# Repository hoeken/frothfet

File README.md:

This is the hardware design repository for FrothFET.

For detailed documentation, please visit the [FrothFET documentation](https://frothfet.com).

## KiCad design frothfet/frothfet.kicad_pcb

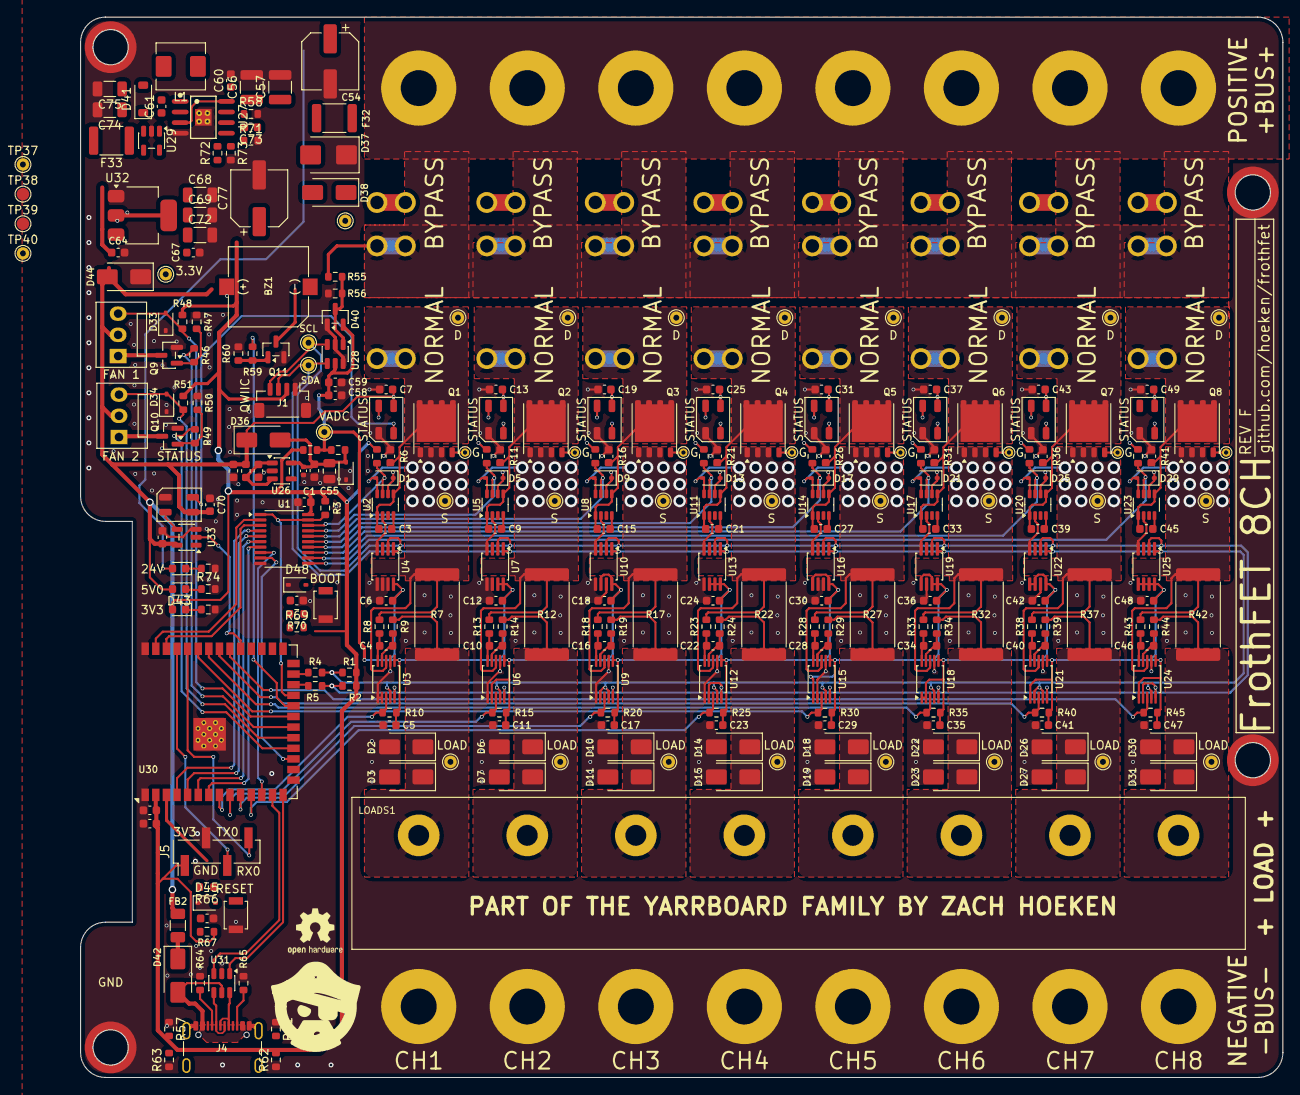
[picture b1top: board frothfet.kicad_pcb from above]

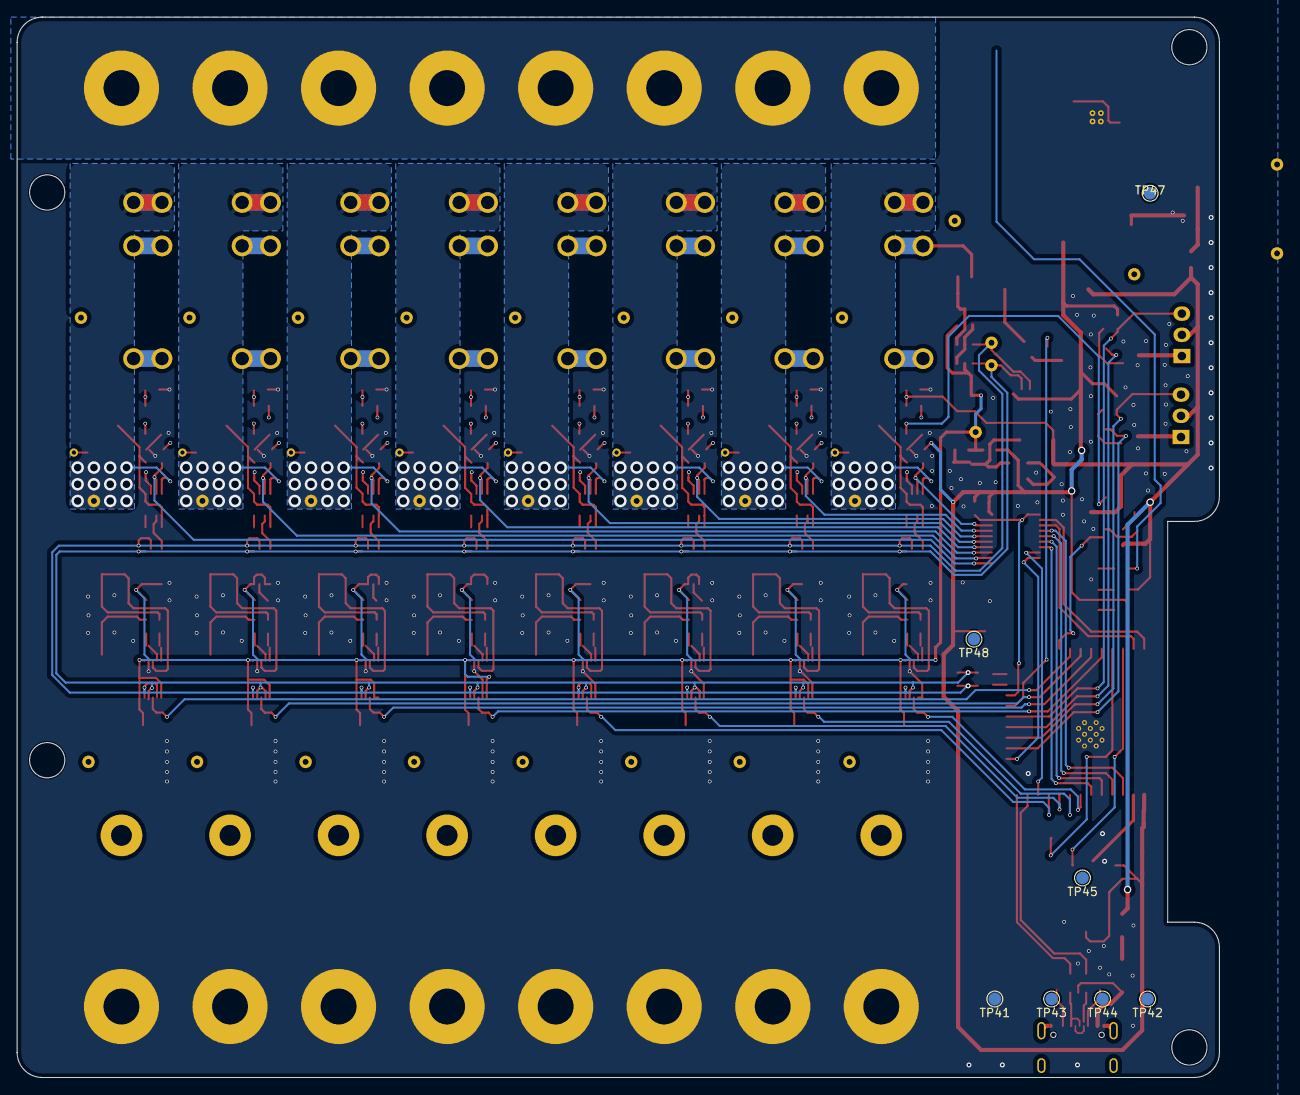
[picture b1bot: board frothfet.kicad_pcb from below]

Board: 4 copper layers, 144.0 x 127.0 mm, 344 parts (9 on the bottom side), 142 nets.

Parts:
ATC1: 20A; ATC Fuse
BZ1: Buzzer; Buzzer_FUET_9.6x9.6
C1, C2, C4, C5, C6, C7, C8, C10, C11, C12, C13, C14, C16, C17, C18, C19, C20, C22, C23, C24, C25, C26, C28, C29, C30, C31, C32, C34, C35, C36, C37, C38, C40, C41, C42, C43, C44, C46, C47, C48, C49, C51, C53, C59, C60, C61, C63, C65, C70: 100nF; C_0603_1608Metric
C3, C9, C15, C21, C27, C33, C39, C45: 220nF; C_0603_1608Metric
C50, C64, C66, C71: 1uF; C_0603_1608Metric
C52: 1nF; C_0402_1005Metric
C54: 100uF/50v; CP_Elec_6.3x7.7
C55: 10uF; C_0805_2012Metric
C56, C57: 10uF; C_1210_3225Metric
C58: 10uF; C_0603_1608Metric
C62: 22uF; C_0603_1608Metric
C67: 4.7uF; C_0603_1608Metric
C68, C69, C72: 100uF / 6.3v; C_1206_3216Metric
C73: 2.7nF; C_0603_1608Metric
C74, C75: 22uF; C_1206_3216Metric
C77: 220uF / 16v; CP_Elec_6.3x5.4
D1, D5, D9, D13, D17, D21, D25, D29: BZT52C20S; D_SOD-323
D2, D6, D10, D14, D18, D22, D26, D30, D36, D38: SS54; D_SMA
D3, D7, D11, D15, D19, D23, D27, D31: SMAJ30CA; D_SMA
D4, D8, D12, D16, D20, D24, D28, D32, D47: WS2812B-Mini; LED_WS2812B-Mini_PLCC4_3.5x3.5mm
D33, D34, D39, D45, D48: PESD3V3L1BA; D_SOD-323
D35, D43, D46: GREEN; LED_0603_1608Metric
D37: SMBJ30CA; D_SMB
D40: BAV199; SOT-23
D41: 1N4148W; D_SOD-123
D42: SS34; D_SMA
D44: SMAJ5.0A; D_SMA
F1, F2, F3, F5, F6, F7, F9, F10, F11, F13, F14, F15, F17, F18, F19, F21, F22, F23, F25, F26, F27, F29, F30, F31: T508; XFCN T508
F4, F8, F12, F16, F20, F24, F28: 20A; ATC Fuse
F32: 500mA; Fuse_1812_4532Metric
F33: mSMD200; Fuse_1812_4532Metric
FB1: BLM18AG121SN1D; L_0603_1608Metric
FB2: 1.5A; Fuse_1206_3216Metric
H1, H2, H3, H4: SMTSO30XXX
J1: Conn_01x04_MountingPin; JST_SH_BM04B-SRSS-TB_1x04-1MP_P1.00mm_Vertical
J2: Screw_Terminal_01x08; Frothfet Busbar Positive Rev E
J3: Screw_Terminal_01x08; Frothfet Busbar Negative Rev E
J4: USB_TYPE_C_16PIN; USB_C_Receptacle_GCT_USB4105-xx-A_16P_TopMnt_Horizontal
J5: Conn_01x04; PinHeader_1x04_P2.54mm_Vertical_SMD_Pin1Left
L1: 6.8uH; L_Chilisin_BMRA00050530
LOADS1: Screw_Terminal_01x08; KF78S-13.0-8P
LOGO1: Logo_Open_Hardware_Small; Logo Small
LOGO2: Logo_Open_Hardware_Small; OSHW-Logo2_7.3x6mm_SilkScreen
M1, M2: Fan_Tacho; FanPinHeader_1x03_P2.54mm_Vertical
Q1, Q2, Q3, Q4, Q5, Q6, Q7, Q8: BSC010N04LS; Infineon_PG-TDSON-8_6.15x5.15mm
Q9, Q10, Q11: AO3400A; SOT-23
R1, R2: 2.2k; R_0603_1608Metric
R3, R6, R10, R11, R15, R16, R20, R21, R25, R26, R30, R31, R35, R36, R40, R41, R45, R48, R51, R67, R70, R74: 10k; R_0603_1608Metric
R4, R5, R53, R54, R57, R61, R62, R63: 0R; R_0603_1608Metric
R7, R12, R17, R22, R27, R32, R37, R42: 2 mOhm; R_4020_10251Metric
R8, R9, R13, R14, R18, R19, R23, R24, R28, R29, R33, R34, R38, R39, R43, R44: 4.7R 1%; R_0603_1608Metric
R46, R49, R59, R66, R69: 100R; R_0603_1608Metric
R47, R50, R52, R60: 100k; R_0603_1608Metric
R55: 300K 0.1%; R_0603_1608Metric
R56: 22K 0.1%; R_0603_1608Metric
R58: 82k 1%; R_0603_1608Metric
R64, R65, R68: 5.1k; R_0603_1608Metric
R71: 24k; R_0603_1608Metric
R72: 62k 1%; R_0603_1608Metric
R73: 11.8k 1%; R_0603_1608Metric
SW1, SW2: SW_SPST_B3U-1000P
TP1, TP2, TP4, TP5, TP6, TP8, TP9, TP10, TP12, TP13, TP14, TP16, TP17, TP18, TP20, TP21, TP22, TP24, TP25, TP26, TP28, TP29, TP30, TP32, TP33, TP34, TP35, TP36, TP37, TP40, TP46: TestPoint_THTPad_D1.5mm_Drill0.7mm
TP3, TP7, TP11, TP15, TP19, TP23, TP27, TP31: TestPoint_THTPad_D1.0mm_Drill0.5mm
TP38, TP39, TP41, TP42, TP43, TP44, TP45, TP47, TP48: TestPoint; TestPoint_Pad_D1.5mm
U1: 74LVC541A; TSSOP-20_4.4x6.5mm_P0.65mm
U2, U5, U8, U11, U14, U17, U20, U23: LM74502H; SOT-23-8
U3, U6, U9, U12, U15, U18, U21, U24: INA226; VSSOP-10_3x3mm_P0.5mm
U4, U7, U10, U13, U16, U19, U22, U25: LM75BD; MSOP-8_3x3mm_P0.65mm
U26: TPS7A2033PDBVR; SOT-23-5
U27: RT7272BGSP; SOIC-8_L5.0-W4.0-P1.27-LS6.0-BL-EP2.0
U28: MCP3425A0T-ECH; SOT-23-6
U29: MAX40200AUK; SOT-23-5
U30: ESP32-S3-WROOM-1-N16R8; ESP32-S3-WROOM-1
U31: USBLC6-2SC6; SOT-23-6
U32: LDL1117S33R; SOT-223-3_TabPin2
U33: SN74LV1T34DBV; SOT-23-5

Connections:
+3.3V: C1.1, C62.1, C63.1, C67.1, C68.1, C69.1, C72.1, D46.2 (A), J1.2, J5.1, R1.2, R2.2, R3.1, R6.2, R11.2, R16.2, R21.2, R26.2, R31.2, R36.2, R41.2, R48.2, R51.2, R54.2, R67.1, R70.2, TP46.1, TP47.1, U1.20 (VCC), U30.2 (3V3), U32.2 (VO)
+3.3VADC: C5.1, C6.1, C11.1, C12.1, C17.1, C18.1, C23.1, C24.1, C29.1, C30.1, C35.1, C36.1, C41.1, C42.1, C47.1, C48.1, C58.1, C59.1, D40.2 (K), R10.2, R15.2, R20.2, R25.2, R30.2, R35.2, R40.2, R45.2, R53.2, R54.1, TP36.1, U3.6 (VS), U4.8 (+Vs), U6.2 (A0), U6.6 (VS), U7.7 (A0), U7.8 (+Vs), U9.6 (VS), U10.6 (A1), U10.8 (+Vs), U12.6 (VS), U13.6 (A1), U13.7 (A0), U13.8 (+Vs), U15.1 (A1), U15.6 (VS), U16.5 (A2), U16.8 (+Vs), U18.1 (A1), U18.2 (A0), U18.6 (VS), U19.5 (A2), U19.7 (A0), U19.8 (+Vs), U21.1 (A1), U21.6 (VS), U22.5 (A2), U22.6 (A1), U22.8 (+Vs), U24.1 (A1), U24.6 (VS), U25.5 (A2), U25.6 (A1), U25.7 (A0), U25.8 (+Vs), U28.5 (Vdd)
+5V: BZ1.1 (+), C7.2, C13.2, C19.2, C25.2, C31.2, C37.2, C43.2, C49.2, C50.1, C64.1, C65.1, C70.1, C77.1, D4.1 (VDD), D8.1 (VDD), D12.1 (VDD), D16.1 (VDD), D20.1 (VDD), D24.1 (VDD), D28.1 (VDD), D32.1 (VDD), D36.1 (K), D43.2 (A), D44.2 (A2), D47.1 (VDD), FB1.1, FB2.2, M1.2 (+), M2.2 (+), TP39.1, TP40.1, U29.5 (OUT), U32.3 (VI), U33.5 (VCC)
+24V: C54.1, F2.1, F6.1, F10.1, F14.1, F18.1, F22.1, F26.1, F30.1, F32.2, J2.1, J2.2, J2.3, J2.4, J2.5, J2.6, J2.7, J2.8, R55.2
/CHANNEL 1/LED_DOUT: D4.2 (DOUT), D8.4 (DIN)
/CHANNEL 1/LOAD_SWITCHED: D1.2 (A), F3.1, Q1.3 (S), R7.1, R8.2, TP5.1, U2.8 (SRC), U3.8 (Vbus)
/CHANNEL 1/LOAD_VSS: C2.1, C3.1, F1.1, Q1.1 (D), TP4.1, U2.1 (EN/UVLO), U2.5 (VS)
/CHANNEL 2/LED_DOUT: D8.2 (DOUT), D12.4 (DIN)
/CHANNEL 2/LOAD_SWITCHED: D5.2 (A), F7.1, Q2.3 (S), R12.1, R13.2, TP9.1, U5.8 (SRC), U6.8 (Vbus)
/CHANNEL 2/LOAD_VSS: C8.1, C9.1, F5.1, Q2.1 (D), TP8.1, U5.1 (EN/UVLO), U5.5 (VS)
/CHANNEL 3/LED_DOUT: D12.2 (DOUT), D16.4 (DIN)
/CHANNEL 3/LOAD_SWITCHED: D9.2 (A), F11.1, Q3.3 (S), R17.1, R18.2, TP13.1, U8.8 (SRC), U9.8 (Vbus)
/CHANNEL 3/LOAD_VSS: C14.1, C15.1, F9.1, Q3.1 (D), TP12.1, U8.1 (EN/UVLO), U8.5 (VS)
/CHANNEL 4/LED_DOUT: D16.2 (DOUT), D20.4 (DIN)
/CHANNEL 4/LOAD_SWITCHED: D13.2 (A), F15.1, Q4.3 (S), R22.1, R23.2, TP17.1, U11.8 (SRC), U12.8 (Vbus)
/CHANNEL 4/LOAD_VSS: C20.1, C21.1, F13.1, Q4.1 (D), TP16.1, U11.1 (EN/UVLO), U11.5 (VS)
/CHANNEL 5/LED_DOUT: D20.2 (DOUT), D24.4 (DIN)
/CHANNEL 5/LOAD_SWITCHED: D17.2 (A), F19.1, Q5.3 (S), R27.1, R28.2, TP21.1, U14.8 (SRC), U15.8 (Vbus)
/CHANNEL 5/LOAD_VSS: C26.1, C27.1, F17.1, Q5.1 (D), TP20.1, U14.1 (EN/UVLO), U14.5 (VS)
/CHANNEL 6/LED_DOUT: D24.2 (DOUT), D28.4 (DIN)
/CHANNEL 6/LOAD_SWITCHED: D21.2 (A), F23.1, Q6.3 (S), R32.1, R33.2, TP25.1, U17.8 (SRC), U18.8 (Vbus)
/CHANNEL 6/LOAD_VSS: C32.1, C33.1, F21.1, Q6.1 (D), TP24.1, U17.1 (EN/UVLO), U17.5 (VS)
/CHANNEL 7/LED_DOUT: D28.2 (DOUT), D32.4 (DIN)
/CHANNEL 7/LOAD_SWITCHED: D25.2 (A), F27.1, Q7.3 (S), R37.1, R38.2, TP29.1, U20.8 (SRC), U21.8 (Vbus)
/CHANNEL 7/LOAD_VSS: C38.1, C39.1, F25.1, Q7.1 (D), TP28.1, U20.1 (EN/UVLO), U20.5 (VS)
/CHANNEL 8/LOAD_SWITCHED: D29.2 (A), F31.1, Q8.3 (S), R42.1, R43.2, TP33.1, U23.8 (SRC), U24.8 (Vbus)
/CHANNEL 8/LOAD_VSS: C44.1, C45.1, F29.1, Q8.1 (D), TP32.1, U23.1 (EN/UVLO), U23.5 (VS)
/ESP32-S3/CC1_1: J4.A5 (CC1), R64.1
/ESP32-S3/CC2_1: J4.B5 (CC2), R65.1
/ESP32-S3/EN: R66.2, TP45.1, U30.3 (EN)
/ESP32-S3/ESP_RXD0: J5.4, U30.36 (RXD0)
/ESP32-S3/ESP_TXD0: J5.3, U30.37 (TXD0)
/ESP32-S3/ESP_USB+: U30.14 (USB_D+), U31.1 (I/O1)
/ESP32-S3/ESP_USB-: U30.13 (USB_D-), U31.3 (I/O2)
/ESP32-S3/GPIO0_BOOT: R69.2, TP48.1, U30.27 (IO0)
/ESP32-S3/GPIO1: U1.2 (A0), U30.39 (IO1)
/ESP32-S3/GPIO2: U1.3 (A1), U30.38 (IO2)
/ESP32-S3/GPIO4: U1.4 (A2), U30.4 (IO4)
/ESP32-S3/GPIO5: U1.5 (A3), U30.5 (IO5)
/ESP32-S3/GPIO6: U1.6 (A4), U30.6 (IO6)
/ESP32-S3/GPIO7: U1.7 (A5), U30.7 (IO7)
/ESP32-S3/GPIO8: U1.8 (A6), U30.12 (IO8)
/ESP32-S3/GPIO9: U1.9 (A7), U30.17 (IO9)
/ESP32-S3/GPIO21: R3.2, U1.1 (G1), U1.19 (G2), U30.23 (IO21)
/ESP32-S3/GPIO38: U30.31 (IO38), U33.2 (A)
/ESP32-S3/GPIO47: R4.1, U30.24 (IO47)
/ESP32-S3/GPIO48: R5.2, U30.25 (IO48)
/ESP32-S3/USB_D+: J4.A6 (D+), J4.B6 (D+), TP43.1, U31.6 (I/O1)
/ESP32-S3/USB_D-: J4.A7 (D-), J4.B7 (D-), TP44.1, U31.4 (I/O2)
/ESP32-S3/VBUS: D42.2 (A), J4.A4 (VBUS), J4.A9 (VBUS), J4.B4 (VBUS), J4.B9 (VBUS), TP42.1, U31.5 (VBUS)
/Power Supply/SW: C61.2, L1.1, U27.1 (SW)
ALERT1: R10.1, U3.3 (~Alert), U30.8 (IO15)
ALERT2: R15.1, U6.3 (~Alert), U30.9 (IO16)
ALERT3: R20.1, U9.3 (~Alert), U30.10 (IO17)
ALERT4: R25.1, U12.3 (~Alert), U30.11 (IO18)
ALERT5: R30.1, U15.3 (~Alert), U30.35 (IO42)
ALERT6: R35.1, U18.3 (~Alert), U30.34 (IO41)
ALERT7: R40.1, U21.3 (~Alert), U30.33 (IO40)
ALERT8: R45.1, U24.3 (~Alert), U30.32 (IO39)
CHANNEL_LEDS: D4.4 (DIN), D47.2 (DOUT)
FAN_MOSFET1: R46.2, U30.20 (IO12)
FAN_MOSFET2: R49.2, U30.18 (IO10)
FAN_TACH1: D33.2 (A2), M1.3 (Tacho), R48.1, U30.21 (IO13)
FAN_TACH2: D34.2 (A2), M2.3 (Tacho), R51.1, U30.19 (IO11)
GND: C1.2, C2.2, C5.2, C6.2, C7.1, C8.2, C11.2, C12.2, C13.1, C14.2, C17.2, C18.2, C19.1, C20.2, C23.2, C24.2, C25.1, C26.2, C29.2, C30.2, C31.1, C32.2, C35.2, C36.2, C37.1, C38.2, C41.2, C42.2, C43.1, C44.2, C47.2, C48.2, C49.1, C50.2, C51.2, C52.2, C53.2, C54.2, C55.2, C56.2, C57.2, C58.2, C59.2, C60.2, C62.2, C63.2, C64.2, C65.2, C66.2, C67.2, C68.2, C69.2, C70.2, C71.1, C72.2, C74.2, C75.2, C77.2, D2.2 (A), D3.2 (A2), D4.3 (VSS), D6.2 (A), D7.2 (A2), D8.3 (VSS), D10.2 (A), D11.2 (A2), D12.3 (VSS), D14.2 (A), D15.2 (A2), D16.3 (VSS), D18.2 (A), D19.2 (A2), D20.3 (VSS), D22.2 (A), D23.2 (A2), D24.3 (VSS), D26.2 (A), D27.2 (A2), D28.3 (VSS), D30.2 (A), D31.2 (A2), D32.3 (VSS), D33.1 (A1), D34.1 (A1), D37.1 (A1), D39.1 (A1), D40.1 (A), D44.1 (A1), D45.1 (A1), D47.3 (VSS), D48.1 (A1), H1.1, H2.1, H3.1, H4.1, J1.1, J1.MP (MountPin), J3.1, J3.2, J3.3, J3.4, J3.5, J3.6, J3.7, J3.8, J4.A1 (GND), J4.A12 (GND), J4.B1 (GND), J4.B12 (GND), J5.2, Q9.2 (S), Q10.2 (S), Q11.2 (S), R47.2, R50.2, R52.2, R56.1, R57.1, R58.2, R60.2, R61.1, R62.1, R63.1, R64.2, R65.2, R68.2, R71.2, R73.2, R74.2, SW1.2, SW2.2, TP41.1, U1.10 (GND), U2.2 (GND), U3.1 (A1), U3.2 (A0), U3.7 (GND), U4.4 (GND), U4.5 (A2), U4.6 (A1), U4.7 (A0), U5.2 (GND), U6.1 (A1), U6.7 (GND), U7.4 (GND), U7.5 (A2), U7.6 (A1), U8.2 (GND), U9.1 (A1), U9.7 (GND), U10.4 (GND), U10.5 (A2), U10.7 (A0), U11.2 (GND), U12.1 (A1), U12.7 (GND), U13.4 (GND), U13.5 (A2), U14.2 (GND), U15.2 (A0), U15.7 (GND), U16.4 (GND), U16.6 (A1), U16.7 (A0), U17.2 (GND), U18.7 (GND), U19.4 (GND), U19.6 (A1), U20.2 (GND), U21.7 (GND), U22.4 (GND), U22.7 (A0), U23.2 (GND), U24.7 (GND), U25.4 (GND), U26.2 (GND), U27.4 (GND), U28.2 (Vss), U28.6 (Vin-), U29.2 (GND), U30.1 (GND), U30.40 (GND), U30.41 (GND), U31.2 (GND), U32.1 (GND), U33.3 (GND)
LOAD1: D2.1 (K), D3.1 (A1), LOADS1.1, R7.2, R9.2, TP6.1
LOAD2: D6.1 (K), D7.1 (A1), LOADS1.2, R12.2, R14.2, TP10.1
LOAD3: D10.1 (K), D11.1 (A1), LOADS1.3, R17.2, R19.2, TP14.1
LOAD4: D14.1 (K), D15.1 (A1), LOADS1.4, R22.2, R24.2, TP18.1
LOAD5: D18.1 (K), D19.1 (A1), LOADS1.5, R27.2, R29.2, TP22.1
LOAD6: D22.1 (K), D23.1 (A1), LOADS1.6, R32.2, R34.2, TP26.1
LOAD7: D26.1 (K), D27.1 (A1), LOADS1.7, R37.2, R39.2, TP30.1
LOAD8: D30.1 (K), D31.1 (A1), LOADS1.8, R42.2, R44.2, TP34.1
unnamed: BZ1.2 (-), Q11.3 (D)
unnamed: C73.1, R71.1
unnamed: D1.1 (K), Q1.2 (G), TP3.1, U2.6 (GATE)
unnamed: D5.1 (K), Q2.2 (G), TP7.1, U5.6 (GATE)
unnamed: D9.1 (K), Q3.2 (G), TP11.1, U8.6 (GATE)
unnamed: D13.1 (K), Q4.2 (G), TP15.1, U11.6 (GATE)
unnamed: D17.1 (K), Q5.2 (G), TP19.1, U14.6 (GATE)
unnamed: D21.1 (K), Q6.2 (G), TP23.1, U17.6 (GATE)
unnamed: D25.1 (K), Q7.2 (G), TP27.1, U20.6 (GATE)
unnamed: D29.1 (K), Q8.2 (G), TP31.1, U23.6 (GATE)
unnamed: D35.2 (A), D37.2 (A2), D38.2 (A), F32.1, TP35.1
unnamed: D35.1 (K), R52.1
unnamed: C52.1, C53.1, C55.1, D36.2 (A), D39.2 (A2), R53.1, U26.5 (OUT)
unnamed: C56.1, C57.1, C60.1, D38.1 (K), U27.3 (EN), U27.8 (VIN)
unnamed: D40.3 (COM), R55.1, R56.2, U28.1 (Vin+)
unnamed: C74.1, C75.1, D41.2 (A), F33.2, L1.2, R72.1, TP37.1
unnamed: C61.1, D41.1 (K), U27.2 (BOOT)
unnamed: D42.1 (K), FB2.1
unnamed: D43.1 (K), R74.1
unnamed: C66.1, D45.2 (A2), R66.1, R67.2, SW1.1
unnamed: D46.1 (K), R68.1
unnamed: D47.4 (DIN), U33.4 (Y)
unnamed: C71.2, D48.2 (A2), R69.1, R70.1, SW2.1
unnamed: J4.S1 (SHIELD), R57.2, R61.2, R62.2, R63.2
unnamed: M1.1 (-), Q9.3 (D)
unnamed: M2.1 (-), Q10.3 (D)
unnamed: Q9.1 (G), R46.1, R47.1
unnamed: Q10.1 (G), R49.1, R50.1
unnamed: Q11.1 (G), R59.1, R60.1
unnamed: C3.2, U2.4 (VCAP)
unnamed: C4.1, R8.1, U3.10 (Vin+)
unnamed: C4.2, R9.1, U3.9 (Vin-)
unnamed: C9.2, U5.4 (VCAP)
unnamed: C10.1, R13.1, U6.10 (Vin+)
unnamed: C10.2, R14.1, U6.9 (Vin-)
unnamed: C15.2, U8.4 (VCAP)
unnamed: C16.1, R18.1, U9.10 (Vin+)
unnamed: C16.2, R19.1, U9.9 (Vin-)
unnamed: C21.2, U11.4 (VCAP)
unnamed: C22.1, R23.1, U12.10 (Vin+)
unnamed: C22.2, R24.1, U12.9 (Vin-)
unnamed: C27.2, U14.4 (VCAP)
unnamed: C28.1, R28.1, U15.10 (Vin+)
unnamed: C28.2, R29.1, U15.9 (Vin-)
unnamed: C33.2, U17.4 (VCAP)
unnamed: C34.1, R33.1, U18.10 (Vin+)
unnamed: C34.2, R34.1, U18.9 (Vin-)
unnamed: C39.2, U20.4 (VCAP)
unnamed: C40.1, R38.1, U21.10 (Vin+)
unnamed: C40.2, R39.1, U21.9 (Vin-)
unnamed: C45.2, U23.4 (VCAP)
unnamed: C46.1, R43.1, U24.10 (Vin+)
unnamed: C46.2, R44.1, U24.9 (Vin-)
unnamed: C51.1, FB1.2, U26.1 (IN), U26.3 (EN)
unnamed: C73.2, U27.6 (COMP)
unnamed: R72.2, R73.1, U27.5 (FB)
unnamed: R58.1, U27.7 (RLIM)
unnamed: F33.1, TP38.1, U29.1 (VDD), U29.3 (EN)
PIEZO: R59.2, U30.22 (IO14)
PWM1: R6.1, U1.18 (Y0), U2.7 (OV)
PWM2: R11.1, U1.17 (Y1), U5.7 (OV)
PWM3: R16.1, U1.16 (Y2), U8.7 (OV)
PWM4: R21.1, U1.15 (Y3), U11.7 (OV)
PWM5: R26.1, U1.14 (Y4), U14.7 (OV)
PWM6: R31.1, U1.13 (Y5), U17.7 (OV)
PWM7: R36.1, U1.12 (Y6), U20.7 (OV)
PWM8: R41.1, U1.11 (Y7), U23.7 (OV)
SCL: J1.4, R2.1, R4.2, TP1.1, U3.5 (SCL), U4.2 (SCL), U6.5 (SCL), U7.2 (SCL), U9.5 (SCL), U10.2 (SCL), U12.2 (A0), U12.5 (SCL), U13.2 (SCL), U15.5 (SCL), U16.2 (SCL), U18.5 (SCL), U19.2 (SCL), U21.5 (SCL), U22.2 (SCL), U24.2 (A0), U24.5 (SCL), U25.2 (SCL), U28.3 (SCL)
SDA: J1.3, R1.1, R5.1, TP2.1, U3.4 (SDA), U4.1 (SDA), U6.4 (SDA), U7.1 (SDA), U9.2 (A0), U9.4 (SDA), U10.1 (SDA), U12.4 (SDA), U13.1 (SDA), U15.4 (SDA), U16.1 (SDA), U18.4 (SDA), U19.1 (SDA), U21.2 (A0), U21.4 (SDA), U22.1 (SDA), U24.4 (SDA), U25.1 (SDA), U28.4 (SDA)

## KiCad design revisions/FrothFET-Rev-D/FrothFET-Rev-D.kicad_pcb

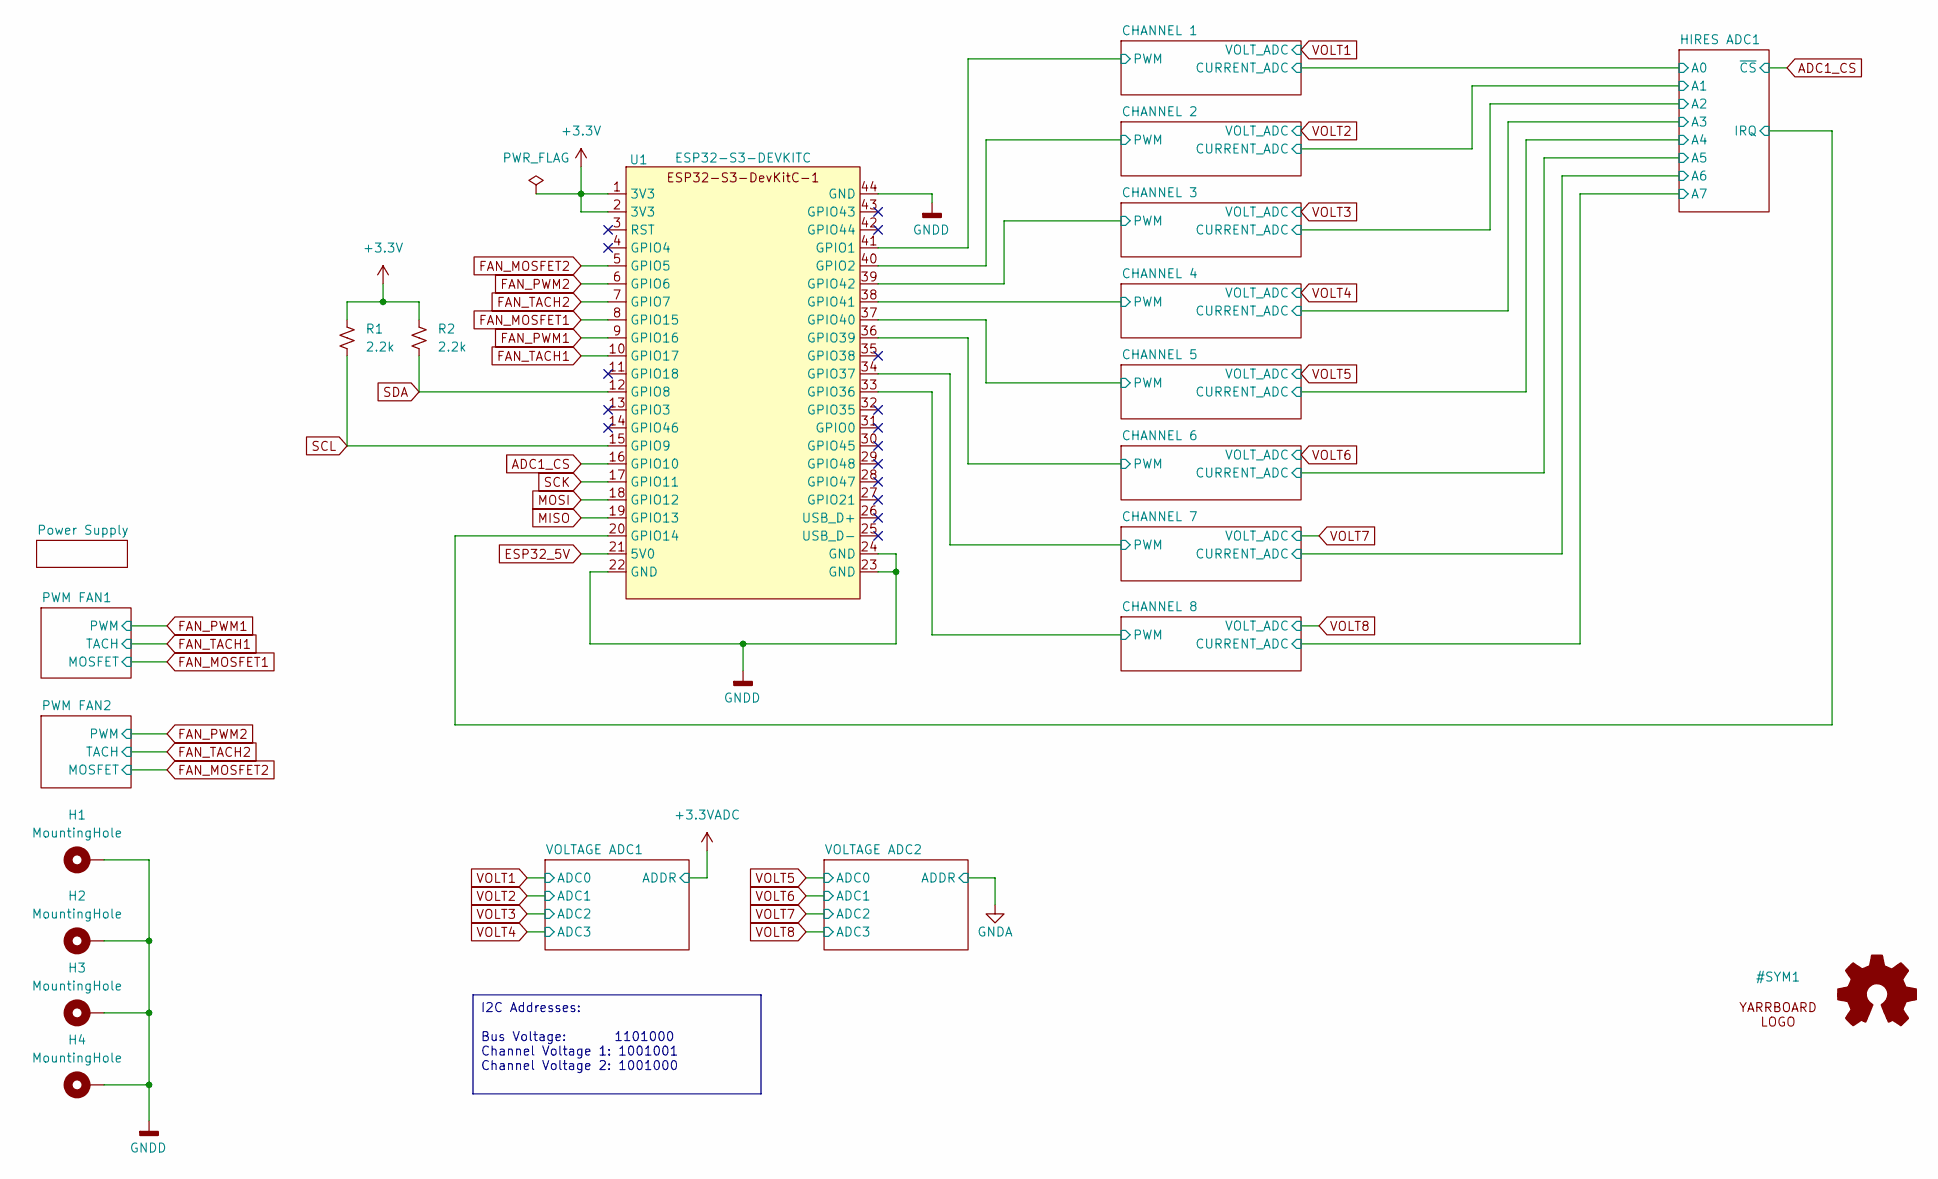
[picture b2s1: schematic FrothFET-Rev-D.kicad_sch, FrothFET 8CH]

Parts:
H1, H2, H3, H4: MountingHole; MountingHole_3.2mm_M3_DIN965_Pad
LOGO1: Logo_Open_Hardware_Small; OSHW-Logo2_14.6x12mm_SilkScreen
R1, R2: 2.2k; R_0805_2012Metric_Pad1.20x1.40mm_HandSolder; LCSC C114561
U1: ESP32-S3-DEVKITC; Waveshare-ESP32-S3-dev-kit

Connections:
+3.3V: R1.2, R2.2, U1.1 (3V3), U1.2 (3V3); also elsewhere on the board
/CHANNEL 1/PWM: U1.41 (GPIO1); also elsewhere on the board
/CHANNEL 2/PWM: U1.40 (GPIO2); also elsewhere on the board
/CHANNEL 3/PWM: U1.39 (GPIO42); also elsewhere on the board
/CHANNEL 4/PWM: U1.38 (GPIO41); also elsewhere on the board
/CHANNEL 5/PWM: U1.37 (GPIO40); also elsewhere on the board
/CHANNEL 6/PWM: U1.36 (GPIO39); also elsewhere on the board
/CHANNEL 7/PWM: U1.34 (GPIO37); also elsewhere on the board
/CHANNEL 8/PWM: U1.33 (GPIO36); also elsewhere on the board
/HIRES ADC1/IRQ: U1.20 (GPIO14); also elsewhere on the board
ADC1_CS: U1.16 (GPIO10); also elsewhere on the board
ESP32_5V: U1.21 (5V0); also elsewhere on the board
FAN_MOSFET1: U1.8 (GPIO15); also elsewhere on the board
FAN_MOSFET2: U1.5 (GPIO5); also elsewhere on the board
FAN_PWM1: U1.9 (GPIO16); also elsewhere on the board
FAN_PWM2: U1.6 (GPIO6); also elsewhere on the board
FAN_TACH1: U1.10 (GPIO17); also elsewhere on the board
FAN_TACH2: U1.7 (GPIO7); also elsewhere on the board
GND: H1.1, H2.1, H3.1, H4.1, U1.22 (GND), U1.23 (GND), U1.24 (GND), U1.44 (GND); also elsewhere on the board
MISO: U1.19 (GPIO13); also elsewhere on the board
MOSI: U1.18 (GPIO12); also elsewhere on the board
SCK: U1.17 (GPIO11); also elsewhere on the board
SCL: R1.1, U1.15 (GPIO9); also elsewhere on the board
SDA: R2.1, U1.12 (GPIO8); also elsewhere on the board

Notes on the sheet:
I2C Addresses: Bus Voltage: 1101000 Channel Voltage 1: 1001001 Channel Voltage 2: 1001000

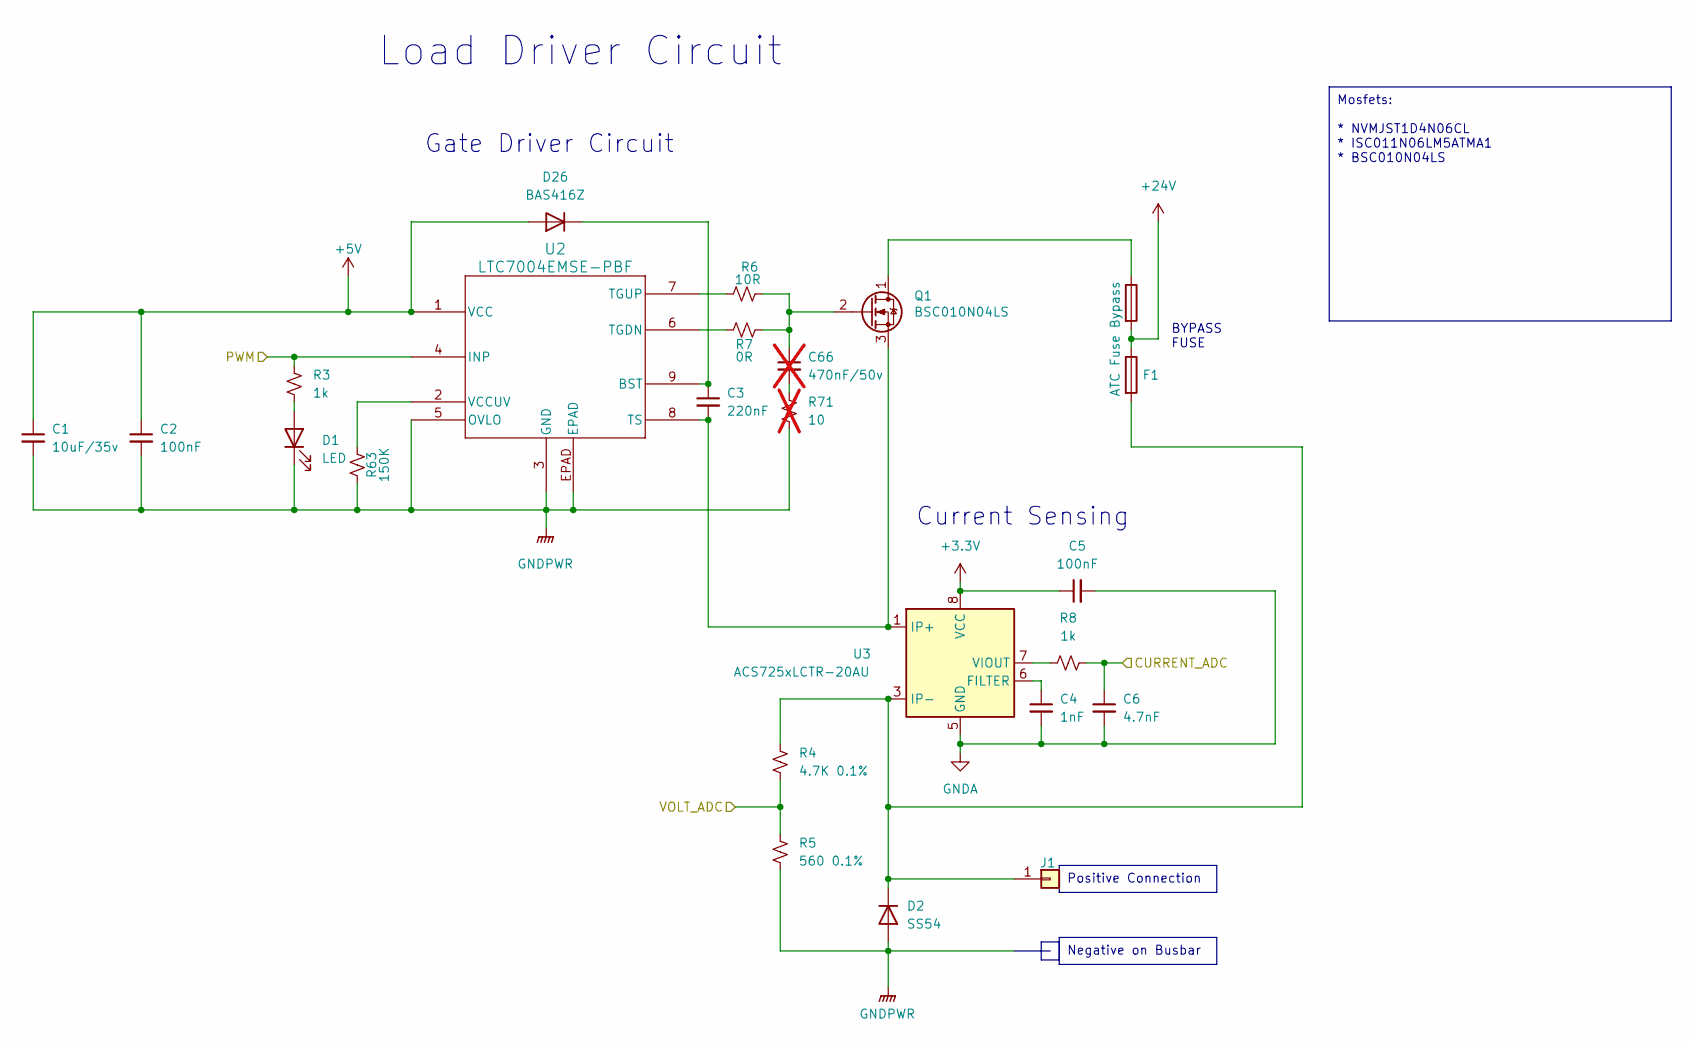
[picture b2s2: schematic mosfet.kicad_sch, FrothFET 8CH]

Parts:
C1: 10uF/35v; C_1206_3216Metric_Pad1.33x1.80mm_HandSolder; LCSC C454102
C2, C5: 100nF; C_0805_2012Metric_Pad1.18x1.45mm_HandSolder; LCSC C49678
C3: 220nF; C_0805_2012Metric_Pad1.18x1.45mm_HandSolder; LCSC C49678
C4: 1nF; C_0805_2012Metric_Pad1.18x1.45mm_HandSolder; Mouser C0805C102J1HACTU
C6: 4.7nF; C_0805_2012Metric_Pad1.18x1.45mm_HandSolder; Mouser C0805C472K5RAC
C66: 470nF/50v; C_0805_2012Metric_Pad1.18x1.45mm_HandSolder; LCSC C106843; not fitted
D1: LED; LED_0805_2012Metric_Pad1.15x1.40mm_HandSolder; LCSC C125094
D2: SS54; D_SMA; LCSC C22452
D26: BAS416Z; D_SOD-323F; Mouser 771-BAS416Z
F1: ATC Fuse Bypass; ATC Bypass Fuse; Mouser 534-3522-3
J1: Conn_01x01; T44001; LCSC C481447
Q1: BSC010N04LS; Infineon_PG-TDSON-8_6.15x5.15mm; LCSC C501508
R3, R8: 1k; R_0805_2012Metric_Pad1.20x1.40mm_HandSolder; LCSC C95781
R4: 4.7K 0.1%; R_0805_2012Metric_Pad1.20x1.40mm_HandSolder; LCSC C865386
R5: 560 0.1%; R_0805_2012Metric_Pad1.20x1.40mm_HandSolder; LCSC C865312
R6: 10R; R_0805_2012Metric_Pad1.20x1.40mm_HandSolder; LCSC C96345
R7: 0R; R_0805_2012Metric_Pad1.20x1.40mm_HandSolder; LCSC C96345
R63: 150K; R_0805_2012Metric_Pad1.20x1.40mm_HandSolder; LCSC C96345
R71: 10; R_0805_2012Metric_Pad1.20x1.40mm_HandSolder; LCSC C95781; not fitted
U2: LTC7004EMSE-PBF; MSE_10_ADI; LCSC C690105
U3: ACS725xLCTR-20AU; ACS7XX; Mouser 250-725LLCTR20AUT

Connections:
+3.3V: C5.1, U3.8 (VCC); also elsewhere on the board
+5V: C1.1, C2.1, D26.2 (A), U2.1 (VCC); also elsewhere on the board
+24V: F1.2; also elsewhere on the board
/CHANNEL 1/CURRENT_ADC: C6.1, R8.1; also elsewhere on the board
/CHANNEL 1/PWM: R3.1, U2.4 (INP); also elsewhere on the board
GND: C1.2, C2.2, C4.2, C5.2, C6.2, D1.1 (K), D2.2 (A), R5.1, R63.2, R71.2, U2.3 (GND), U2.5 (OVLO), U2.EPAD, U3.5 (GND); also elsewhere on the board
unnamed: C66.2, R71.1
unnamed: D1.2 (A), R3.2
unnamed: D2.1 (K), F1.3, J1.1, R4.2, U3.3 (IP-), U3.4 (IP-)
unnamed: C3.1, D26.1 (K), U2.9 (BST)
unnamed: F1.1, Q1.1 (D)
unnamed: C66.1, Q1.2 (G), R6.1, R7.1
unnamed: C3.2, Q1.3 (S), U2.8 (TS), U3.1 (IP+), U3.2 (IP+)
unnamed: R7.2, U2.6 (TGDN)
unnamed: R6.2, U2.7 (TGUP)
unnamed: R63.1, U2.2 (VCCUV)
unnamed: C4.1, U3.6 (FILTER)
unnamed: R8.2, U3.7 (VIOUT)
VOLT1: R4.1, R5.2; also elsewhere on the board

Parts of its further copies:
C7, C13, C19, C25, C31, C37, C43: 10uF/35v; C_1206_3216Metric_Pad1.33x1.80mm_HandSolder; LCSC C454102
C8, C11, C14, C17, C20, C23, C26, C29, C32, C35, C38, C41, C44, C47: 100nF; C_0805_2012Metric_Pad1.18x1.45mm_HandSolder; LCSC C49678
C9, C15, C21, C27, C33, C39, C45: 220nF; C_0805_2012Metric_Pad1.18x1.45mm_HandSolder; LCSC C49678
C10, C16, C22, C28, C34, C40, C46: 1nF; C_0805_2012Metric_Pad1.18x1.45mm_HandSolder; Mouser C0805C102J1HACTU
C12, C18, C24, C30, C36, C42, C48: 4.7nF; C_0805_2012Metric_Pad1.18x1.45mm_HandSolder; Mouser C0805C472K5RAC
C67, C68, C69, C70, C71, C72, C73: 470nF/50v; C_0805_2012Metric_Pad1.18x1.45mm_HandSolder; LCSC C106843; not fitted
D3, D5, D7, D9, D11, D13, D15: LED; LED_0805_2012Metric_Pad1.15x1.40mm_HandSolder; LCSC C125094
D4, D6, D8, D10, D12, D14, D16: SS54; D_SMA; LCSC C22452
D27, D28, D29, D30, D31, D32, D33: BAS416Z; D_SOD-323F; Mouser 771-BAS416Z
F2, F3, F4, F5, F6, F7, F8: ATC Fuse Bypass; ATC Bypass Fuse; Mouser 534-3522-3
J2, J3, J4, J5, J6, J7, J8: Conn_01x01; T44001; LCSC C481447
Q2, Q3, Q4, Q5, Q6, Q7, Q8: BSC010N04LS; Infineon_PG-TDSON-8_6.15x5.15mm; LCSC C501508
R9, R14, R15, R20, R21, R26, R27, R32, R33, R38, R39, R44, R45, R50: 1k; R_0805_2012Metric_Pad1.20x1.40mm_HandSolder; LCSC C95781
R10, R16, R22, R28, R34, R40, R46: 4.7K 0.1%; R_0805_2012Metric_Pad1.20x1.40mm_HandSolder; LCSC C865386
R11, R17, R23, R29, R35, R41, R47: 560 0.1%; R_0805_2012Metric_Pad1.20x1.40mm_HandSolder; LCSC C865312
R12, R18, R24, R30, R36, R42, R48: 10R; R_0805_2012Metric_Pad1.20x1.40mm_HandSolder; LCSC C96345
R13, R19, R25, R31, R37, R43, R49: 0R; R_0805_2012Metric_Pad1.20x1.40mm_HandSolder; LCSC C96345
R64, R65, R66, R67, R68, R69, R70: 150K; R_0805_2012Metric_Pad1.20x1.40mm_HandSolder; LCSC C96345
R72, R73, R74, R75, R76, R77, R78: 10; R_0805_2012Metric_Pad1.20x1.40mm_HandSolder; LCSC C95781; not fitted
U4, U6, U8, U10, U12, U14, U16: LTC7004EMSE-PBF; MSE_10_ADI; LCSC C690105
U5, U7, U9, U11, U13, U15, U17: ACS725xLCTR-20AU; ACS7XX; Mouser 250-725LLCTR20AUT

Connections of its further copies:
+3.3V: C11.1, C17.1, C23.1, C29.1, C35.1, C41.1, C47.1, U5.8 (VCC), U7.8 (VCC), U9.8 (VCC), U11.8 (VCC), U13.8 (VCC), U15.8 (VCC), U17.8 (VCC); also elsewhere on the board
+5V: C7.1, C8.1, C13.1, C14.1, C19.1, C20.1, C25.1, C26.1, C31.1, C32.1, C37.1, C38.1, C43.1, C44.1, D27.2 (A), D28.2 (A), D29.2 (A), D30.2 (A), D31.2 (A), D32.2 (A), D33.2 (A), U4.1 (VCC), U6.1 (VCC), U8.1 (VCC), U10.1 (VCC), U12.1 (VCC), U14.1 (VCC), U16.1 (VCC); also elsewhere on the board
+24V: F2.2, F3.2, F4.2, F5.2, F6.2, F7.2, F8.2; also elsewhere on the board
/CHANNEL 2/CURRENT_ADC: C12.1, R14.1; also elsewhere on the board
/CHANNEL 2/PWM: R9.1, U4.4 (INP); also elsewhere on the board
/CHANNEL 3/CURRENT_ADC: C18.1, R20.1; also elsewhere on the board
/CHANNEL 3/PWM: R15.1, U6.4 (INP); also elsewhere on the board
/CHANNEL 4/CURRENT_ADC: C24.1, R26.1; also elsewhere on the board
/CHANNEL 4/PWM: R21.1, U8.4 (INP); also elsewhere on the board
/CHANNEL 5/CURRENT_ADC: C30.1, R32.1; also elsewhere on the board
/CHANNEL 5/PWM: R27.1, U10.4 (INP); also elsewhere on the board
/CHANNEL 6/CURRENT_ADC: C36.1, R38.1; also elsewhere on the board
/CHANNEL 6/PWM: R33.1, U12.4 (INP); also elsewhere on the board
/CHANNEL 7/CURRENT_ADC: C42.1, R44.1; also elsewhere on the board
/CHANNEL 7/PWM: R39.1, U14.4 (INP); also elsewhere on the board
/CHANNEL 8/CURRENT_ADC: C48.1, R50.1; also elsewhere on the board
/CHANNEL 8/PWM: R45.1, U16.4 (INP); also elsewhere on the board
GND: C7.2, C8.2, C10.2, C11.2, C12.2, C13.2, C14.2, C16.2, C17.2, C18.2, C19.2, C20.2, C22.2, C23.2, C24.2, C25.2, C26.2, C28.2, C29.2, C30.2, C31.2, C32.2, C34.2, C35.2, C36.2, C37.2, C38.2, C40.2, C41.2, C42.2, C43.2, C44.2, C46.2, C47.2, C48.2, D3.1 (K), D4.2 (A), D5.1 (K), D6.2 (A), D7.1 (K), D8.2 (A), D9.1 (K), D10.2 (A), D11.1 (K), D12.2 (A), D13.1 (K), D14.2 (A), D15.1 (K), D16.2 (A), R11.1, R17.1, R23.1, R29.1, R35.1, R41.1, R47.1, R64.2, R65.2, R66.2, R67.2, R68.2, R69.2, R70.2, R72.2, R73.2, R74.2, R75.2, R76.2, R77.2, R78.2, U4.3 (GND), U4.5 (OVLO), U4.EPAD, U5.5 (GND), U6.3 (GND), U6.5 (OVLO), U6.EPAD, U7.5 (GND), U8.3 (GND), U8.5 (OVLO), U8.EPAD, U9.5 (GND), U10.3 (GND), U10.5 (OVLO), U10.EPAD, U11.5 (GND), U12.3 (GND), U12.5 (OVLO), U12.EPAD, U13.5 (GND), U14.3 (GND), U14.5 (OVLO), U14.EPAD, U15.5 (GND), U16.3 (GND), U16.5 (OVLO), U16.EPAD, U17.5 (GND); also elsewhere on the board
unnamed: C67.2, R72.1
unnamed: C68.2, R73.1
unnamed: C69.2, R74.1
unnamed: C70.2, R75.1
unnamed: C71.2, R76.1
unnamed: C72.2, R77.1
unnamed: C73.2, R78.1
unnamed: D3.2 (A), R9.2
unnamed: D4.1 (K), F2.3, J2.1, R10.2, U5.3 (IP-), U5.4 (IP-)
unnamed: D5.2 (A), R15.2
unnamed: D6.1 (K), F3.3, J3.1, R16.2, U7.3 (IP-), U7.4 (IP-)
unnamed: D7.2 (A), R21.2
unnamed: D8.1 (K), F4.3, J4.1, R22.2, U9.3 (IP-), U9.4 (IP-)
unnamed: D9.2 (A), R27.2
unnamed: D10.1 (K), F5.3, J5.1, R28.2, U11.3 (IP-), U11.4 (IP-)
unnamed: D11.2 (A), R33.2
unnamed: D12.1 (K), F6.3, J6.1, R34.2, U13.3 (IP-), U13.4 (IP-)
unnamed: D13.2 (A), R39.2
unnamed: D14.1 (K), F7.3, J7.1, R40.2, U15.3 (IP-), U15.4 (IP-)
unnamed: D15.2 (A), R45.2
unnamed: D16.1 (K), F8.3, J8.1, R46.2, U17.3 (IP-), U17.4 (IP-)
unnamed: C9.1, D27.1 (K), U4.9 (BST)
unnamed: C15.1, D28.1 (K), U6.9 (BST)
unnamed: C21.1, D29.1 (K), U8.9 (BST)
unnamed: C27.1, D30.1 (K), U10.9 (BST)
unnamed: C33.1, D31.1 (K), U12.9 (BST)
unnamed: C39.1, D32.1 (K), U14.9 (BST)
unnamed: C45.1, D33.1 (K), U16.9 (BST)
unnamed: F2.1, Q2.1 (D)
unnamed: C67.1, Q2.2 (G), R12.1, R13.1
unnamed: C9.2, Q2.3 (S), U4.8 (TS), U5.1 (IP+), U5.2 (IP+)
unnamed: F3.1, Q3.1 (D)
unnamed: C68.1, Q3.2 (G), R18.1, R19.1
unnamed: C15.2, Q3.3 (S), U6.8 (TS), U7.1 (IP+), U7.2 (IP+)
unnamed: F4.1, Q4.1 (D)
unnamed: C69.1, Q4.2 (G), R24.1, R25.1
unnamed: C21.2, Q4.3 (S), U8.8 (TS), U9.1 (IP+), U9.2 (IP+)
unnamed: F5.1, Q5.1 (D)
unnamed: C70.1, Q5.2 (G), R30.1, R31.1
unnamed: C27.2, Q5.3 (S), U10.8 (TS), U11.1 (IP+), U11.2 (IP+)
unnamed: F6.1, Q6.1 (D)
unnamed: C71.1, Q6.2 (G), R36.1, R37.1
unnamed: C33.2, Q6.3 (S), U12.8 (TS), U13.1 (IP+), U13.2 (IP+)
unnamed: F7.1, Q7.1 (D)
unnamed: C72.1, Q7.2 (G), R42.1, R43.1
unnamed: C39.2, Q7.3 (S), U14.8 (TS), U15.1 (IP+), U15.2 (IP+)
unnamed: F8.1, Q8.1 (D)
unnamed: C73.1, Q8.2 (G), R48.1, R49.1
unnamed: C45.2, Q8.3 (S), U16.8 (TS), U17.1 (IP+), U17.2 (IP+)
unnamed: R13.2, U4.6 (TGDN)
unnamed: R12.2, U4.7 (TGUP)
unnamed: R64.1, U4.2 (VCCUV)
unnamed: C10.1, U5.6 (FILTER)
unnamed: R14.2, U5.7 (VIOUT)
unnamed: R19.2, U6.6 (TGDN)
unnamed: R18.2, U6.7 (TGUP)
unnamed: R65.1, U6.2 (VCCUV)
unnamed: C16.1, U7.6 (FILTER)
unnamed: R20.2, U7.7 (VIOUT)
unnamed: R25.2, U8.6 (TGDN)
unnamed: R24.2, U8.7 (TGUP)
unnamed: R66.1, U8.2 (VCCUV)
unnamed: C22.1, U9.6 (FILTER)
unnamed: R26.2, U9.7 (VIOUT)
unnamed: R31.2, U10.6 (TGDN)
unnamed: R30.2, U10.7 (TGUP)
unnamed: R67.1, U10.2 (VCCUV)
unnamed: C28.1, U11.6 (FILTER)
unnamed: R32.2, U11.7 (VIOUT)
unnamed: R37.2, U12.6 (TGDN)
unnamed: R36.2, U12.7 (TGUP)
unnamed: R68.1, U12.2 (VCCUV)
unnamed: C34.1, U13.6 (FILTER)
unnamed: R38.2, U13.7 (VIOUT)
unnamed: R43.2, U14.6 (TGDN)
unnamed: R42.2, U14.7 (TGUP)
unnamed: R69.1, U14.2 (VCCUV)
unnamed: C40.1, U15.6 (FILTER)
unnamed: R44.2, U15.7 (VIOUT)
unnamed: R49.2, U16.6 (TGDN)
unnamed: R48.2, U16.7 (TGUP)
unnamed: R70.1, U16.2 (VCCUV)
unnamed: C46.1, U17.6 (FILTER)
unnamed: R50.2, U17.7 (VIOUT)
VOLT2: R10.1, R11.2; also elsewhere on the board
VOLT3: R16.1, R17.2; also elsewhere on the board
VOLT4: R22.1, R23.2; also elsewhere on the board
VOLT5: R28.1, R29.2; also elsewhere on the board
VOLT6: R34.1, R35.2; also elsewhere on the board
VOLT7: R40.1, R41.2; also elsewhere on the board
VOLT8: R46.1, R47.2; also elsewhere on the board

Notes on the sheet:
Mosfets: * NVMJST1D4N06CL * ISC011N06LM5ATMA1 * BSC010N04LS
Negative on Busbar
Positive Connection
Current Sensing
Load Driver Circuit
BYPASS FUSE
Gate Driver Circuit
